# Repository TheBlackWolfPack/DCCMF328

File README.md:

# DCCMF328
DCC MultiFunctional decoder based on ATmega 328pb.
Created with KiCAD.

## Hardware

## Firmware

## Connections

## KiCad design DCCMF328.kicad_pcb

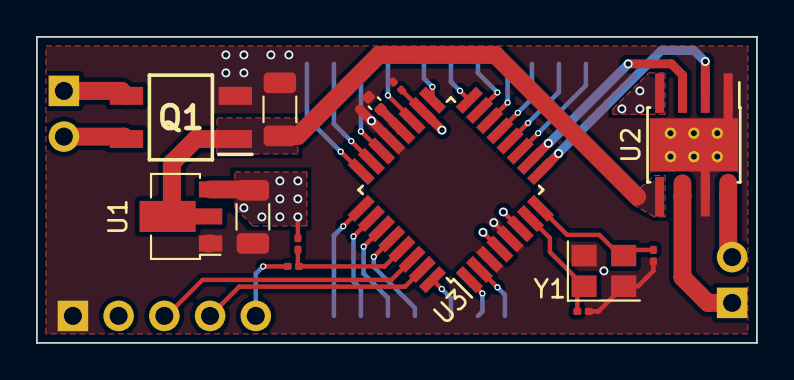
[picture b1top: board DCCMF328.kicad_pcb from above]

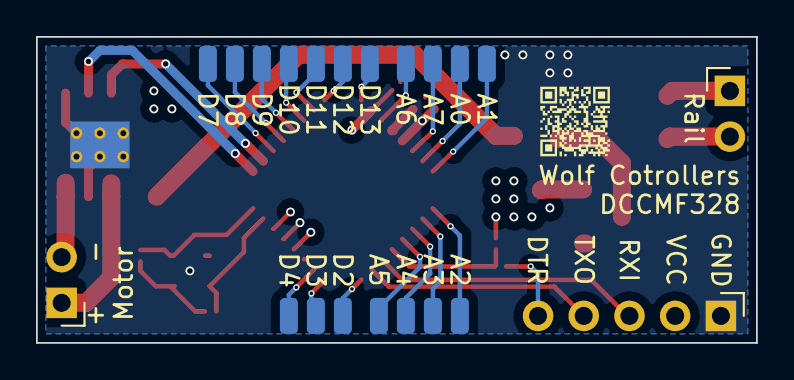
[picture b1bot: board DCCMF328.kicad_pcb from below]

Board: 4 copper layers, 40.0 x 17.0 mm, 34 parts (21 on the bottom side), 34 nets.

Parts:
A0, A1, A2, A3, A4, A5, A6, A7: SolderWirePad_1x01_SMD_1x2mm
C1, C2: 10uF; C_1206_3216Metric
C3, C7: 0.1uF; C_0201_0603Metric
C4: 0.1nF; C_0402_1005Metric
C5, C6: 8.1pF; C_0201_0603Metric
D2, D3, D4, D7, D8, D9, D10, D11, D12, D13: SolderWirePad_1x01_SMD_1x2mm
J1, J2: Conn_01x02_Male; PinHeader_1x02_P2.54mm_Horizontal
J3: Conn_01x05_Male; PinHeader_1x05_P2.54mm_Horizontal
Q1: MB10S; SOP240P700X300-4N
R1: 10K; R_0201_0603Metric
U1: HT7550-1-SOT89; SOT-89-3
U2: DRV8870DDA; Texas_HTSOP-8-1EP_3.9x4.9mm_P1.27mm_EP2.95x4.9mm_Mask2.4x3.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
U3: ATmega328PB-A; TQFP-32_7x7mm_P0.8mm
Y1: Crystal_GND24; Crystal_SMD_3225-4Pin_3.2x2.5mm

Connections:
A0: A0.1, U3.23 (PC0)
A1: A1.1, U3.24 (PC1)
A2: A2.1, U3.25 (PC2)
A3: A3.1, U3.26 (PC3)
A4/SDA: A4.1, U3.27 (PC4)
A5/SCL: A5.1, U3.28 (PC5)
A6: A6.1, U3.19 (PE2)
A7: A7.1, U3.22 (PE3)
D2: D2.1, U3.32 (PD2)
D3: D3.1, U3.1 (PD3)
D4: D4.1, U3.2 (PD4)
D5: U2.2 (IN2), U3.9 (PD5)
D6: U2.3 (IN1), U3.10 (PD6)
D7: D7.1, U3.11 (PD7)
D8: D8.1, U3.12 (PB0)
D9: D9.1, U3.13 (PB1)
D10: D10.1, U3.14 (PB2)
D11/MOSI: D11.1, U3.15 (PB3)
D12/MISO: D12.1, U3.16 (PB4)
D13/SCK: D13.1, U3.17 (PB5)
DTR: C7.2, J3.5
GND: C1.2, C2.2, C3.1, C4.1, C5.1, C6.1, J3.1, Q1.2 (-), U1.1 (GND), U2.1 (GND), U2.7 (ISEN), U2.9 (GND), U3.3 (PE0), U3.5 (GND), U3.21 (GND), Y1.2, Y1.4
Motor+: J2.1, U2.6 (OUT1)
Motor-: J2.2, U2.8 (OUT2)
unnamed: C4.2, U3.20 (AREF)
unnamed: C5.2, U3.7 (XTAL1/PB6), Y1.1
unnamed: C6.2, U3.8 (XTAL2/PB7), Y1.3
RESET: C7.1, R1.1, U3.29 (~RESET/PC6)
RXI: J3.3, U3.30 (PD0)
Rail_1: J1.2, Q1.4 (~_2)
Rail_2: J1.1, Q1.3 (~_1)
TXO: J3.4, U3.31 (PD1)
VCC: C2.1, C3.2, J3.2, R1.2, U1.3 (VOUT), U2.4 (VREF), U3.4 (VCC), U3.6 (PE1), U3.18 (AVCC)
Vdrive: C1.1, Q1.1 (+), U1.2 (VIN), U2.5 (VM)

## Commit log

2023-04-06 initial design
